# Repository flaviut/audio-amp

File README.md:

A simple 2ch, 25W/ch, audio amplifier based on the [TPA3132D2RHBT amplifier
IC](http://www.ti.com/lit/ds/slos841b/slos841b.pdf)

As of this point in time, this design has not been tested at all.

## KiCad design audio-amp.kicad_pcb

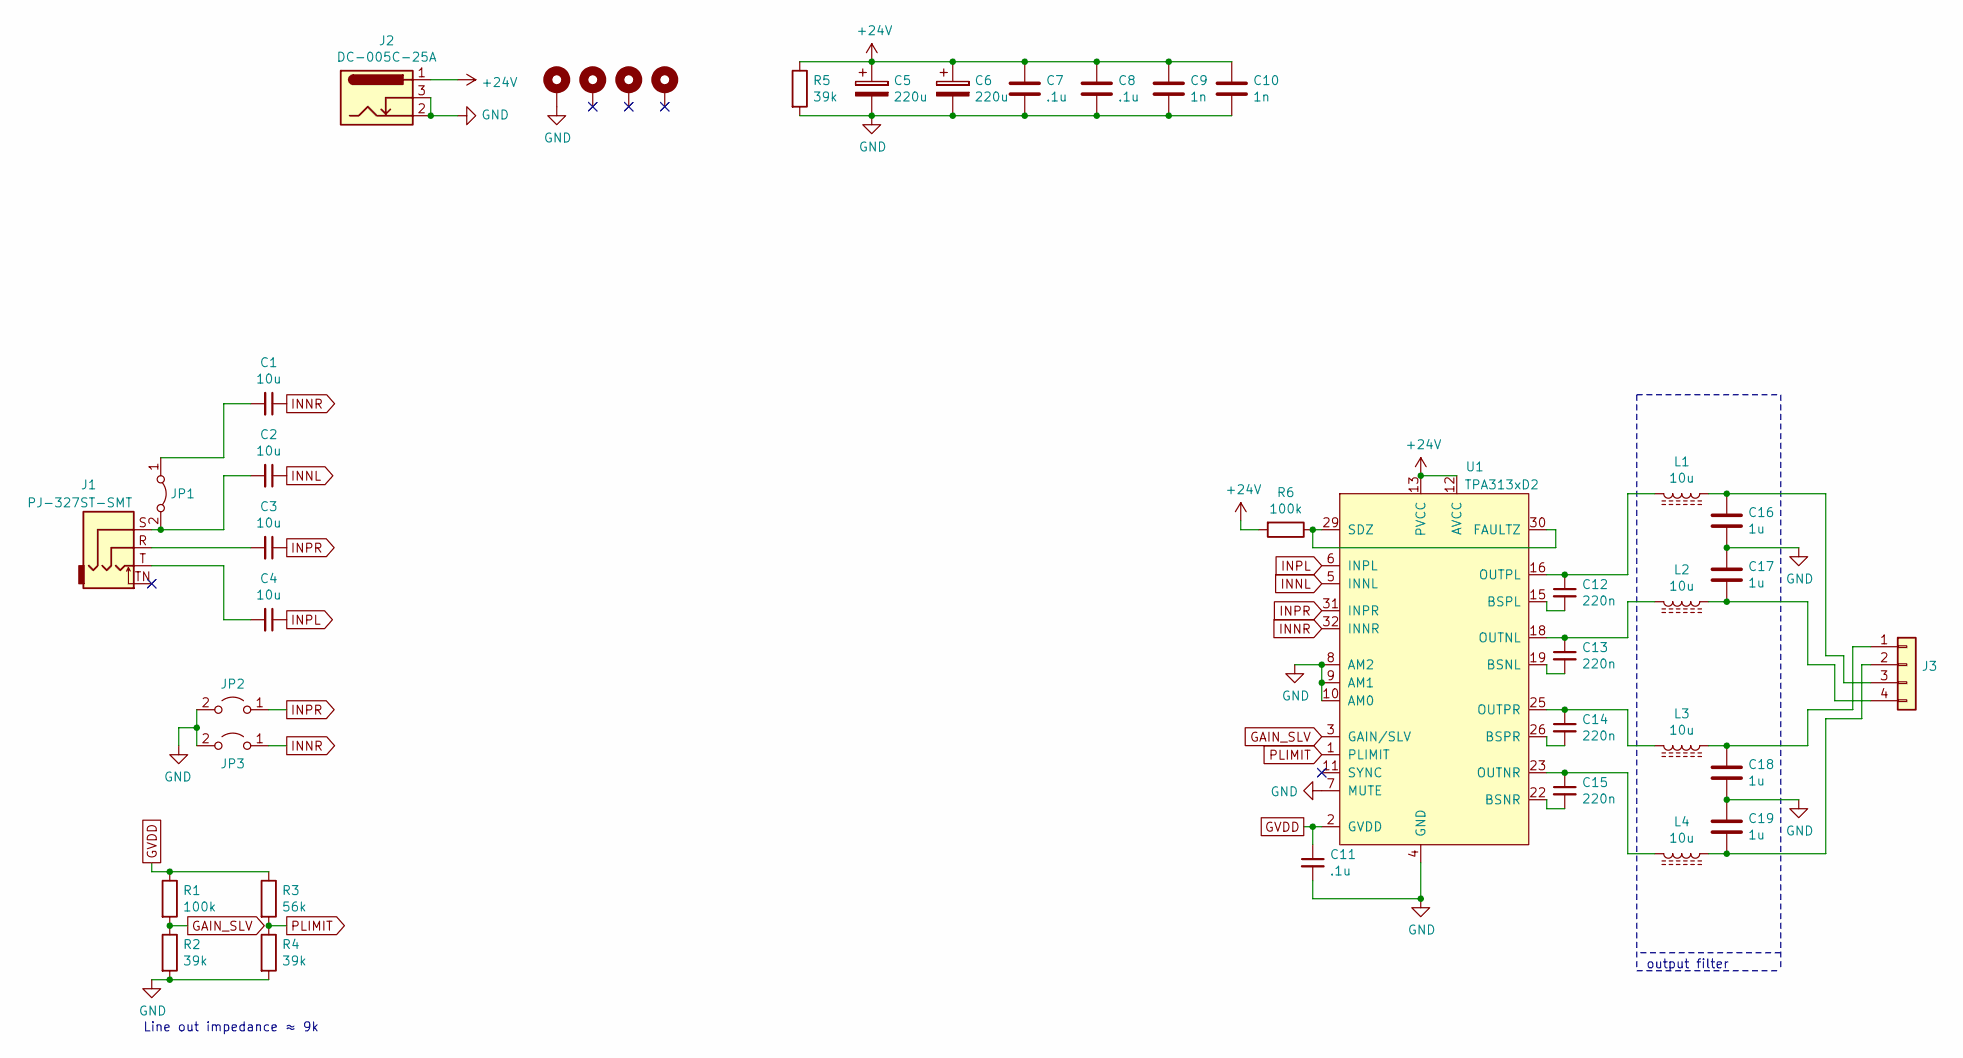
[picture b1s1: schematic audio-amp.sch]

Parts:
C1, C2, C3, C4: 10u; C_0805_2012Metric_Pad1.15x1.40mm_HandSolder
C5, C6: 220u; CP_Elec_6.3x7.7
C7, C8, C11: .1u; C_0603_1608Metric_Pad1.05x0.95mm_HandSolder
C9, C10: 1n; C_0603_1608Metric_Pad1.05x0.95mm_HandSolder
C12, C13, C14, C15: 220n; C_0603_1608Metric_Pad1.05x0.95mm_HandSolder
C16, C17, C18, C19: 1u; C_0603_1608Metric_Pad1.05x0.95mm_HandSolder
H1, H2, H3, H4: MountingHole_Pad; MountingHole_2.2mm_M2_Pad_Via
J1: PJ-327ST-SMT; Jack_3.5mm_PJ31060-I_Horizontal
J2: DC-005C-25A; BarrelJack_Horizontal_DC005C25A
J3: WJ126-5.0; DG301_G-1x04_P5.0mm_Horizontal
JP1: Jumper_2_Bridged; SolderJumper-2_P1.3mm_Open_RoundedPad1.0x1.5mm
JP2, JP3: Jumper_2_Open; SolderJumper-2_P1.3mm_Open_RoundedPad1.0x1.5mm
L1, L2, L3, L4: 10u; L_7.8x7.0_H3.5
R1, R6: 100k; R_0603_1608Metric_Pad1.05x0.95mm_HandSolder
R2, R4, R5: 39k; R_0603_1608Metric_Pad1.05x0.95mm_HandSolder
R3: 56k; R_0603_1608Metric_Pad1.05x0.95mm_HandSolder
U1: TPA313xD2; Texas_S-PVQFN-N32_EP3.45x3.45mm_ThermalVias

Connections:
+24V: C5.1, C6.1, C7.1, C8.1, C9.1, C10.1, J2.1, R5.1, R6.2, U1.12 (AVCC), U1.13 (PVCC), U1.14 (PVCC), U1.27 (PVCC), U1.28 (PVCC)
GAIN_SLV: R1.2, R2.1, U1.3 (GAIN/SLV)
GND: C5.2, C6.2, C7.2, C8.2, C9.2, C10.2, C11.2, C16.2, C17.1, C18.2, C19.1, H1.1, J2.2, J2.3, JP2.2 (B), JP3.2 (B), R2.2, R4.2, R5.2, U1.4 (GND), U1.7 (MUTE), U1.8 (AM2), U1.9 (AM1), U1.10 (AM0), U1.17 (GND), U1.20 (GND), U1.21 (GND), U1.24 (GND), U1.33 (GND)
GVDD: C11.1, R1.1, R3.1, U1.2 (GVDD)
INNL: C2.1, U1.5 (INNL)
INNR: C1.1, JP3.1 (A), U1.32 (INNR)
INPL: C4.1, U1.6 (INPL)
INPR: C3.1, JP2.1 (A), U1.31 (INPR)
unnamed: C1.2, JP1.1 (A)
unnamed: C2.2, J1.S, JP1.2 (B)
unnamed: C3.2, J1.R
unnamed: C4.2, J1.T
unnamed: C12.1, L1.2, U1.16 (OUTPL)
unnamed: C12.2, U1.15 (BSPL)
unnamed: C13.1, L2.2, U1.18 (OUTNL)
unnamed: C13.2, U1.19 (BSNL)
unnamed: C14.1, L3.2, U1.25 (OUTPR)
unnamed: C14.2, U1.26 (BSPR)
unnamed: C15.1, L4.2, U1.23 (OUTNR)
unnamed: C15.2, U1.22 (BSNR)
unnamed: C16.1, J3.3, L1.1
unnamed: C17.2, J3.4, L2.1
unnamed: C18.1, J3.1, L3.1
unnamed: C19.2, J3.2, L4.1
unnamed: R6.1, U1.29 (SDZ), U1.30 (FAULTZ)
PLIMIT: R3.2, R4.1, U1.1 (PLIMIT)

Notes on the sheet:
Line out impedance ≈ 9k
output filter

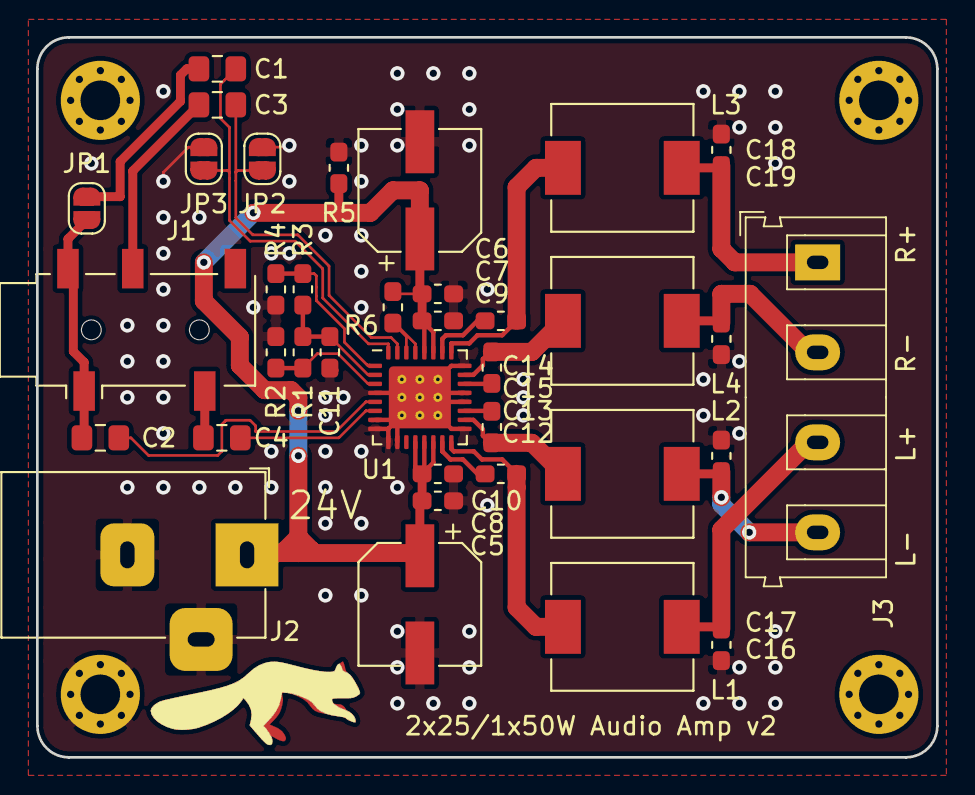
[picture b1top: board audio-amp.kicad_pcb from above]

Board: 2 copper layers, 50.0 x 40.0 mm, 41 parts (0 on the bottom side), 26 nets.

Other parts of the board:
Ref**: Val**; squirrel-pcb

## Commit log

2019-02-10 Add design
2019-02-10 Add datasheets
2019-02-10 Add readme
2019-02-10 Add OSHW logo
2019-02-10 Add screenshot
2019-03-17 progress on v2.
2019-03-21 Rev 2 done (probably)
    This revision has
    1. Correct capacitor filtering, with well-matched differential traces
    2. The fault pin is no longer floating
    3. The fault pin is now tied to the enable pin, allowing for
    auto-restarting every 2 seconds.
    4. The PVCC pin is now connected to power, instead of being left
